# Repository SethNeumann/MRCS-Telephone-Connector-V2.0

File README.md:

# REPO NAME: MRCS0Telephone-Connector-V2.0
## License: Creative Commons Attribution-NonCommercial-ShareAlike

This board provides connectors to extend the MRCS power and phone bus (used by the EBF31A Battery Feed and ATSN Dispatcher/Operator Boards) to as many as 12 stations. Pads are provided for a bucking converter to develop 12VDC for buzzers, LEDs and Relay Latches. I’ve been developing a series of circuit boards to perform the various functions needed to build a layout phone system, but I never made a central board to distribute the phone line and auxiliary power. In the past I assumed the user would use either telephone style “66 blocks” or barrier strips to distribute these signals, but that has become a road block for some users, so this board, with its on board screw terminals puts the basic connections in one place. Features:

• Takes power from the 6-conductor modular telephone and +24V power bus (note to phone people: this is positive 24 to keep things simple for non-phone model railroaders) • Two 6 conductor Jacks are provided for daisy chaining the bus. Connectors are oriented with the locking tab up for easy connection and disconnection.

• Connector pads provide up to 12 connections on 0.100 centers for Tip, Ring, +12 and Ground. If you are assembling your own board and need less connections, you can use screw terminals (or your favorite 0.100 connector) with fewer positions

• Optional auxiliary 6 position screw terminal brings all lines on the bus out for easy access

• Polarity protection diode protects against use of non-reversing (DCC Bus 6 conductor cable)

- 2.1 mm barrel jack for 24vdc input

• Pads for an LM2596 bucking converter which provides 12V for buzzers, LEDs and Relay Latches etc., or you can substitute a boost converter for any voltage up to 35VDC

All components are through-hole technology for ease of assembly and repair.

You are free to download these files and make your own boards or cou can purchase bare boards or assembled and tested product from Model Railroad Control Systems.

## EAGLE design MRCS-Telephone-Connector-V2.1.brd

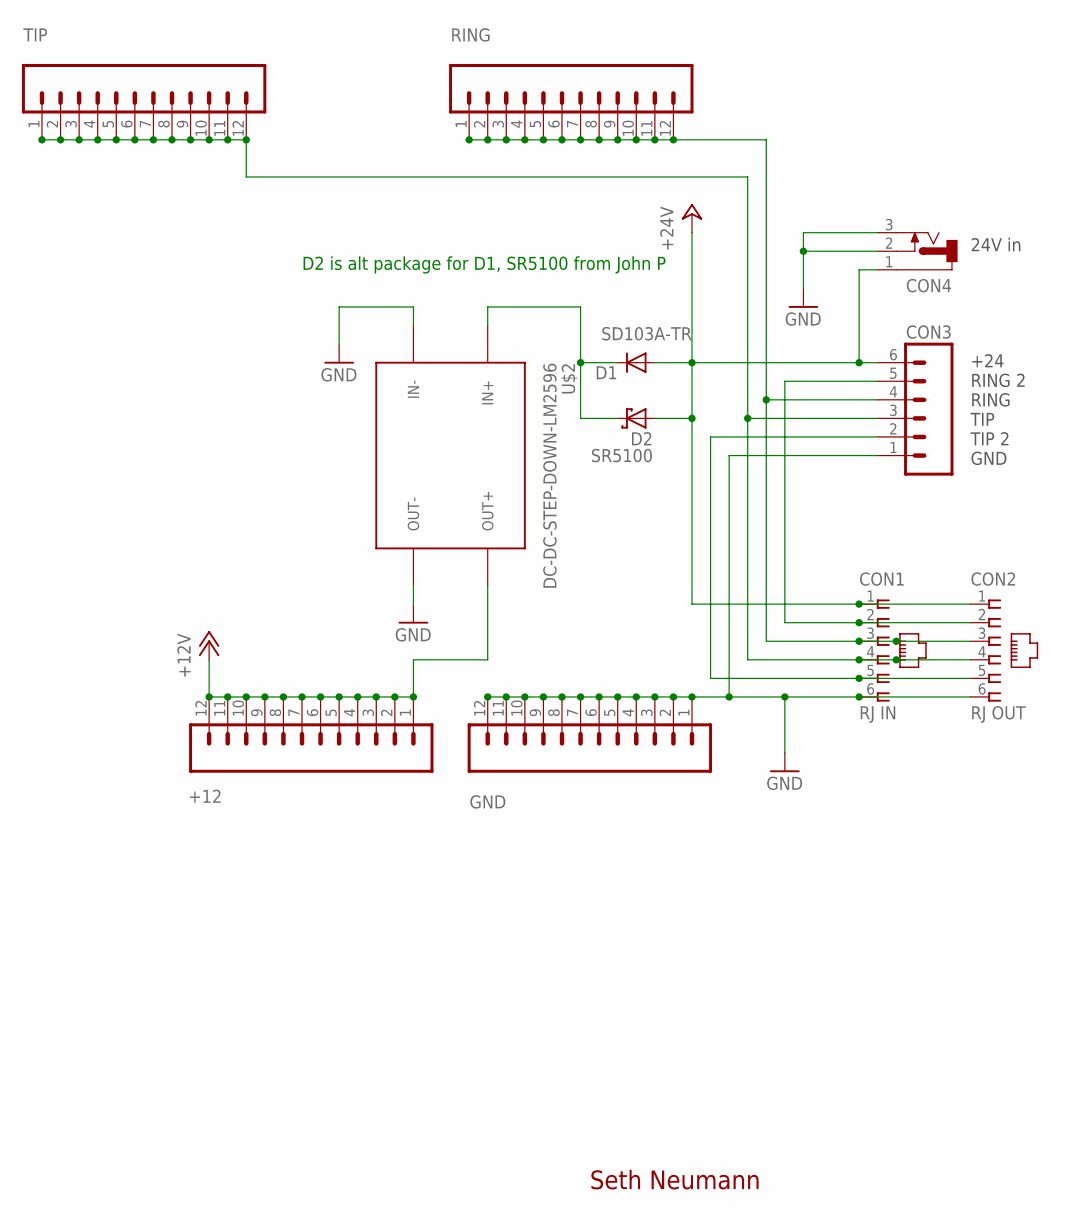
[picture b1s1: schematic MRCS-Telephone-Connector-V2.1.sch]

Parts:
+12: CONNECTOR-M12LOCK; 1X12_LOCK
CON1: RJ IN; RJ25-INVERTED
CON2: RJ OUT; RJ25-INVERTED
CON3: CONNECTOR-M06LOCK; 1X06_LOCK
CON4: CONNECTOR-DC-POWER-RA; DCJ0202
D1: SD103A-TR; DIODE-1N4001
D2: SR5100; AG
GND: CONNECTOR-M12LOCK; 1X12_LOCK
RING: CONNECTOR-M12LOCK; 1X12_LOCK
TIP: CONNECTOR-M12LOCK; 1X12_LOCK
U$2: DC-DC-STEP-DOWN-LM2596

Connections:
+12V: +12.1, +12.2, +12.3, +12.4, +12.5, +12.6, +12.7, +12.8, +12.9, +12.10, +12.11, +12.12, U$2.OUT+
+24V: CON1.1, CON2.1, CON3.6, CON4.1, D1.A, D2.A
GND: CON1.6, CON2.6, CON3.1, CON4.2, CON4.3, GND.1, GND.2, GND.3, GND.4, GND.5, GND.6, GND.7, GND.8, GND.9, GND.10, GND.11, GND.12, U$2.IN-, U$2.OUT-
unnamed: D1.C, D2.C, U$2.IN+
RING: CON1.3, CON2.3, CON3.4, RING.1, RING.2, RING.3, RING.4, RING.5, RING.6, RING.7, RING.8, RING.9, RING.10, RING.11, RING.12
RING2: CON1.2, CON2.2, CON3.5
TIP: CON1.4, CON2.4, CON3.3, TIP.1, TIP.2, TIP.3, TIP.4, TIP.5, TIP.6, TIP.7, TIP.8, TIP.9, TIP.10, TIP.11, TIP.12
TIP2: CON1.5, CON2.5, CON3.2

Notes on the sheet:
Seth Neumann
+24 RING 2 RING TIP TIP 2 GND
24V in
D2 is alt package for D1, SR5100 from John P

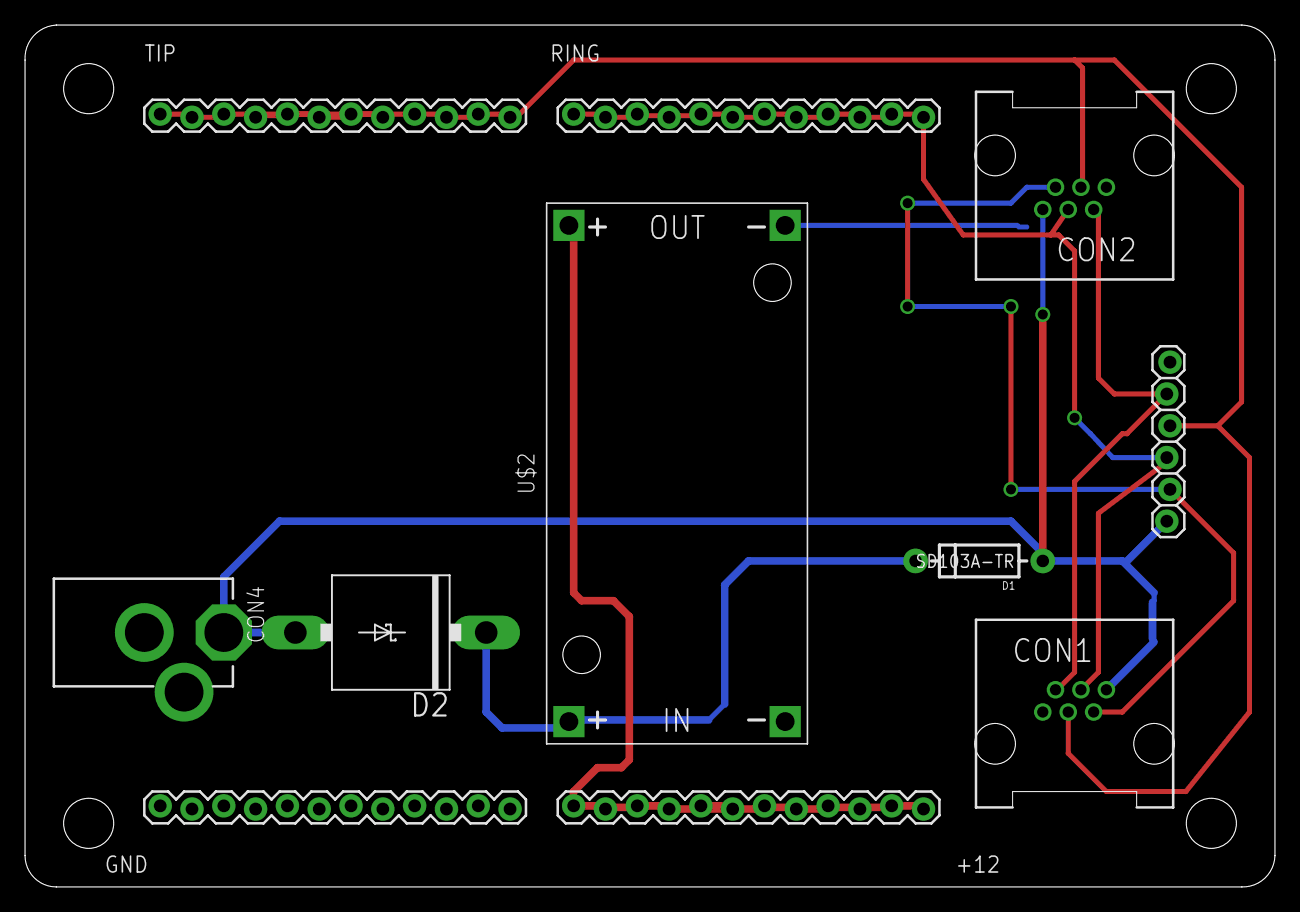
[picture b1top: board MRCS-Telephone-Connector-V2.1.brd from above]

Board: 2 copper layers, 99.8 x 68.8 mm, 15 parts (0 on the bottom side), 8 nets.

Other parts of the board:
U$1: BOARD-DINRAIL-2.71IN-MRCS
U$4: MRCSLOGOTOP
U$5: MRCSLOGOBTM
U$6: CA-PROP65WARNING

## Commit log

2020-09-30 initial commit
    initial commit
2020-09-30 intitial commit
    intial commit
2020-10-01 moved to GitHub
2020-12-20 change to single bucker
    change to single buckers
2023-09-13 changed to version 2.1
    added 5A schottkey diode
2023-09-13 Update INFO
    show production status

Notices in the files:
parts and their libraries:
diy-modules: Released under the Creative Commons Attribution 4.0 International License: http://creativecommons.org/licenses/by/4.0
